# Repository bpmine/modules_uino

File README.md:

# modules_uino
Quelques modules à base d'arduino

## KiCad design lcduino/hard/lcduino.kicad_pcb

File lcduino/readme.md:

# LCDUINO - Ecran LCD Wifi déporté

Cet écran connecté permet d'afficher des informations fournies sur le réseau.

Un bouton permet d'interragir avec l'écran:
- Mise en veille
- Acquittement d'un message
- Réveil

## Mode d'emploi

Le boîtier est connecté en permanence au réseau local. Un serveur ouvert permet à un client du réseau d'envoyer des messages et des commandes à l'écran. Le boîtier est donc toujours accessible.

L'écran passe en veille au bout d'une heure.
Un appui sur le bouton permet de réveiller l'écran.

Un appui long sur le bouton fait passer l'écran en veille.

Lorsqu'un nouveau message est affiché, un symbole indique qu'il n'est pas encore lu. Pour marquer le message comme lu, l'utilisateur appuye brièvement sur le bouton. Le message est alors acquitté.

Un site web est accessible en permanance. Il permet de:
- Indiquer ce qui est actuellement affiché à l'écran
- Indiquer si le dernier message a été acquitté ou non
- Afficher un nouveau message
- Envoyer des commandes (ex: Afficher un chat, un chien, faire bip, ...)

## Carte électronique

Voir le dossier hard

## Logiciel

Voir le dossier src

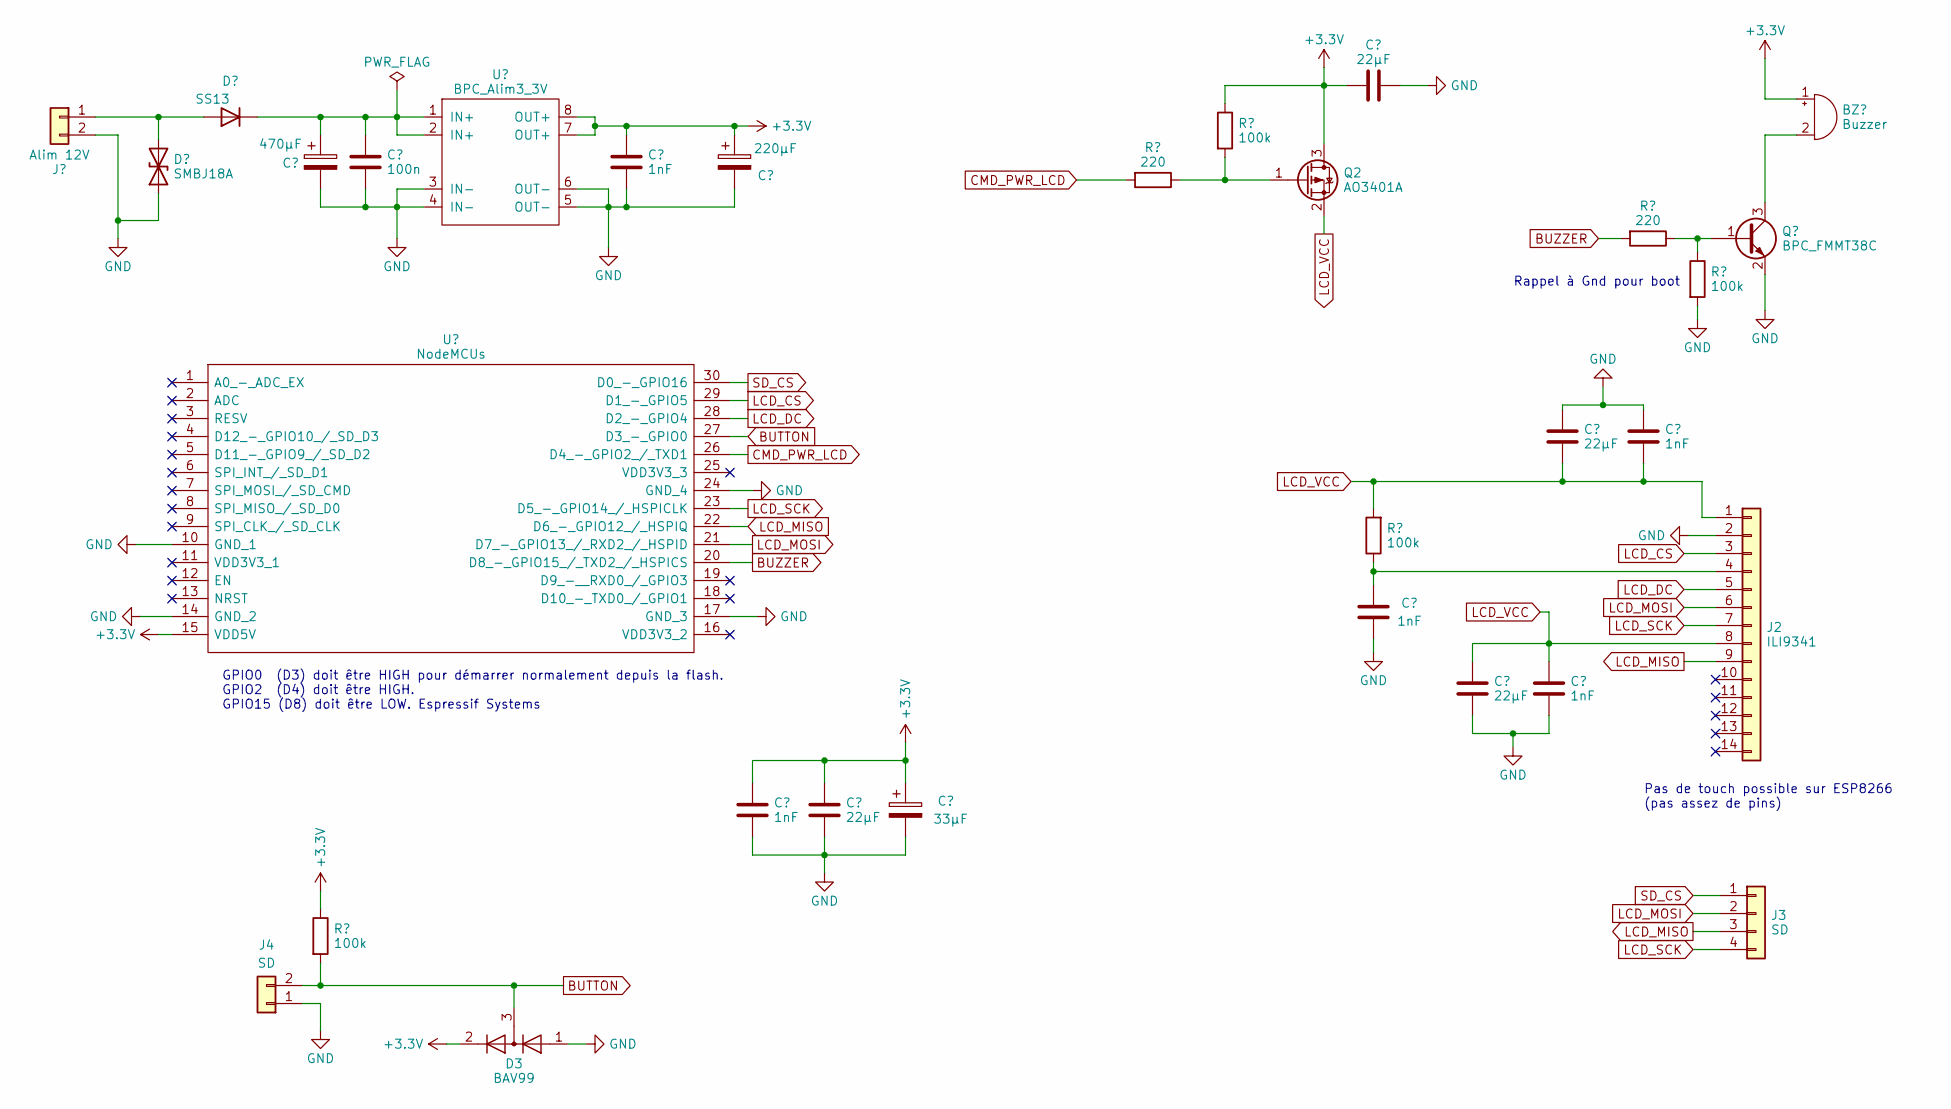
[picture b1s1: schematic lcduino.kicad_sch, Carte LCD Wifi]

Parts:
BZ1: Buzzer; MagneticBuzzer_ProSignal_ABT-410-RC
C1: 470µF; CP_Elec_8x10
C2: 100n; C_0805_2012Metric_Pad1.18x1.45mm_HandSolder
C3, C5, C8, C9, C13: 1nF; C_0805_2012Metric_Pad1.18x1.45mm_HandSolder
C4: 220µF; CP_Elec_6.3x5.3
C6, C10, C11, C12: 22µF; C_1206_3216Metric_Pad1.33x1.80mm_HandSolder
C7: 33µF; CP_Elec_4x5.3
D1: SMBJ18A; D_SMB_Handsoldering
D2: SS13; D_SMA
D3: BAV99; SOT-23
J1: Alim 12V; TerminalBlock_Phoenix_MKDS-1,5-2-5.08_1x02_P5.08mm_Horizont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
J2: ILI9341; PinSocket_1x14_P2.54mm_Vertical
J3: SD; PinSocket_1x04_P2.54mm_Vertical
J4: SD; JST_EH_B2B-EH-A_1x02_P2.50mm_Vertical
Q1: BPC_FMMT38C; BPC_SOT-23-3_HandSoldering
Q2: AO3401A; SOT-23
R1, R3: 220; R_0805_2012Metric_Pad1.20x1.40mm_HandSolder
R2, R4, R5, R6: 100k; R_0805_2012Metric_Pad1.20x1.40mm_HandSolder
U1: NodeMCUs; BPC_NodeMCU_small; Manufacturer_Part_Number 113990105; Mouser Part Number 713-113990105
U2: BPC_Alim3_3V

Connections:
+3.3V: BZ1.1 (-), C3.1, C4.1, C5.1, C6.1, C7.1, C11.1, D3.2 (A), Q2.3 (D), R4.1, R6.1, U1.15 (VDD5V), U2.7 (OUT+), U2.8 (OUT+)
BUTTON: D3.3 (K), J4.2, R6.2, U1.27 (D3_-_GPIO0)
BUZZER: R1.2, U1.20 (D8_-_GPIO15_/_TXD2_/_HSPICS)
CMD_PWR_LCD: R3.2, U1.26 (D4_-_GPIO2_/_TXD1)
GND: C1.2, C2.2, C3.2, C4.2, C5.2, C6.2, C7.2, C8.1, C9.1, C10.1, C11.2, C12.2, C13.2, D1.1 (A1), D3.1 (K), J1.2, J2.2, J4.1, Q1.2 (E), R5.2, U1.10 (GND_1), U1.14 (GND_2), U1.17 (GND_3), U1.24 (GND_4), U2.3 (IN-), U2.4 (IN-), U2.5 (OUT-), U2.6 (OUT-)
LCD_CS: J2.3, U1.29 (D1_-_GPIO5)
LCD_DC: J2.5, U1.28 (D2_-_GPIO4)
LCD_MISO: J2.9, J3.3, U1.22 (D6_-_GPIO12_/_HSPIQ)
LCD_MOSI: J2.6, J3.2, U1.21 (D7_-_GPIO13_/_RXD2_/_HSPID)
LCD_SCK: J2.7, J3.4, U1.23 (D5_-_GPIO14_/_HSPICLK)
LCD_VCC: C9.2, C10.2, C12.1, C13.1, J2.1, J2.8, Q2.2 (S), R2.2
unnamed: BZ1.2 (+), Q1.3 (C)
unnamed: D1.2 (A2), D2.2 (A), J1.1
unnamed: C1.1, C2.1, D2.1 (K), U2.1 (IN+), U2.2 (IN+)
unnamed: C8.2, J2.4, R2.1
unnamed: Q1.1 (B), R1.1, R5.1
unnamed: Q2.1 (G), R3.1, R4.2
SD_CS: J3.1, U1.30 (D0_-_GPIO16)

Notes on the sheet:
GPIO0 (D3) doit être HIGH pour démarrer normalement depuis la flash. GPIO2 (D4) doit être HIGH. GPIO15 (D8) doit être LOW. Espressif Systems
Pas de touch possible sur ESP8266 (pas assez de pins)
Rappel à Gnd pour boot

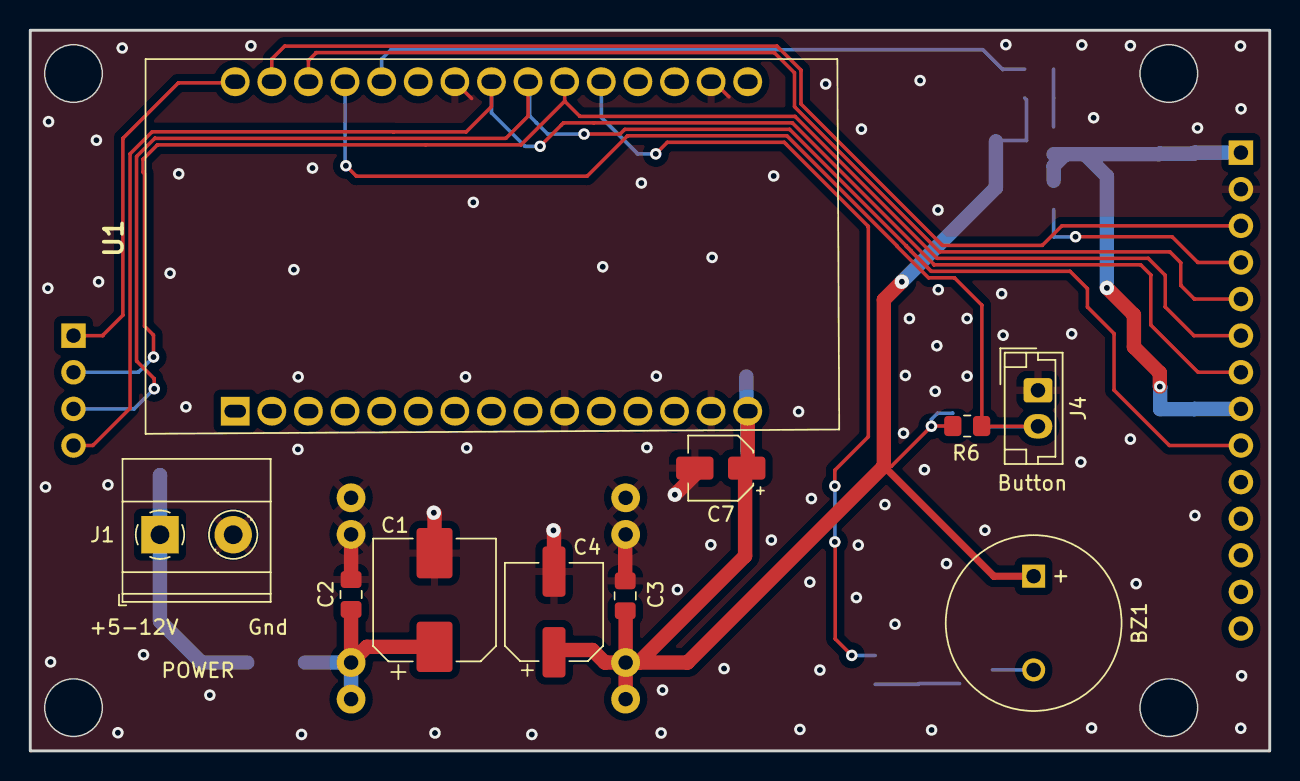
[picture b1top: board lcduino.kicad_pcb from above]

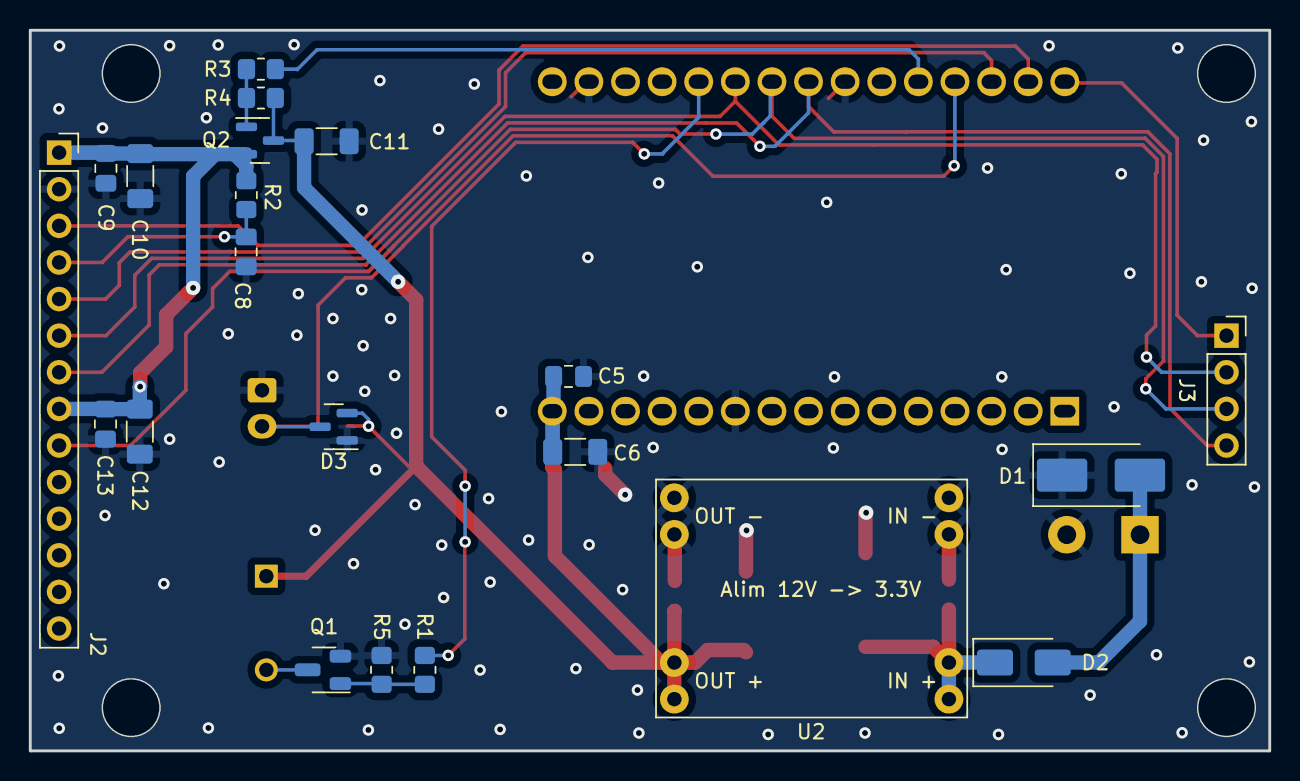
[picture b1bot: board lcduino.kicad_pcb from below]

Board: 2 copper layers, 86.0 x 50.0 mm, 31 parts (21 on the bottom side), 18 nets.

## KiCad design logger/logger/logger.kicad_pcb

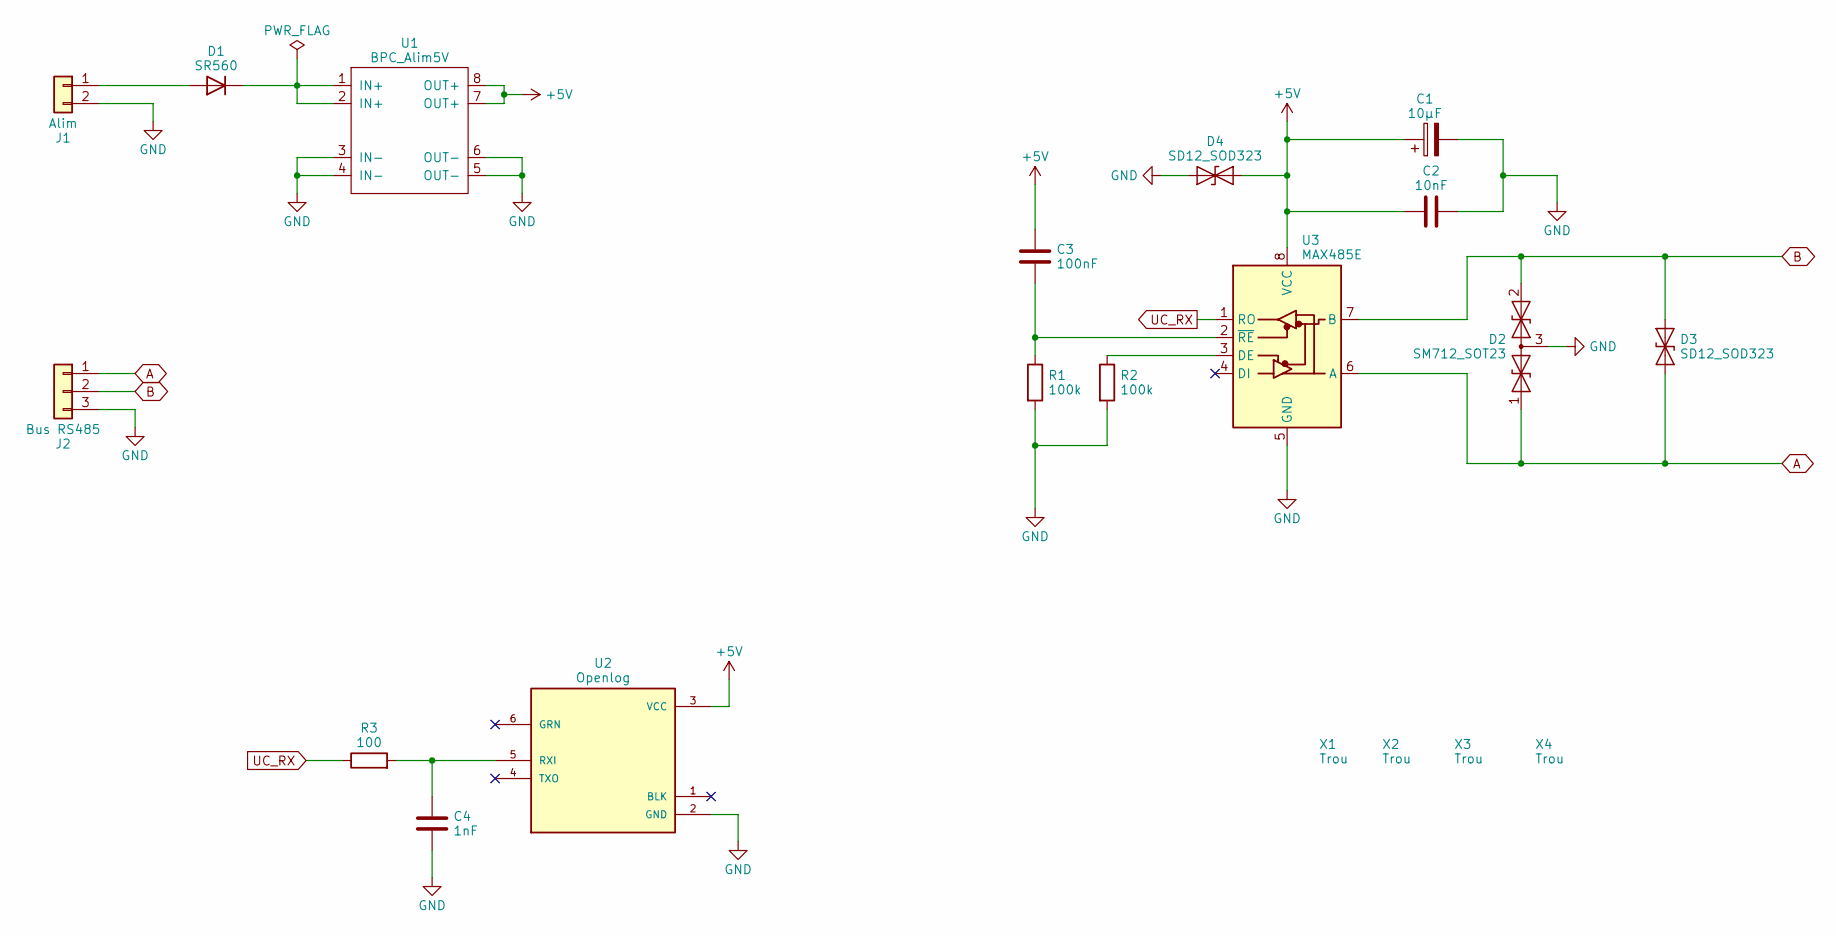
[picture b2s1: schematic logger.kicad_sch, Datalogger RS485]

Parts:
C1: 10µF; C_0805_2012Metric_Pad1.18x1.45mm_HandSolder
C2: 10nF; C_0805_2012Metric_Pad1.18x1.45mm_HandSolder
C3: 100nF; C_0805_2012Metric_Pad1.18x1.45mm_HandSolder
C4: 1nF; C_0805_2012Metric_Pad1.18x1.45mm_HandSolder
D1: SR560; D_DO-15_P12.70mm_Horizontal
D2: SM712_SOT23; SOT-23
D3, D4: SD12_SOD323; D_SOD-323
J1: Alim; TerminalBlock_Phoenix_MPT-0,5-2-2.54_1x02_P2.54mm_Horizontal
J2: Bus RS485; TerminalBlock_Phoenix_MPT-0,5-3-2.54_1x03_P2.54mm_Horizontal
R1, R2: 100k; R_0805_2012Metric_Pad1.20x1.40mm_HandSolder
R3: 100; R_0805_2012Metric_Pad1.20x1.40mm_HandSolder
U1: BPC_Alim5V
U2: Openlog; BPC_openlog; PARTREV v15
U3: MAX485E; BPC_MAX485E_SOIC127P600X175-8N
X1, X2, X3, X4: Trou; BPC_Trou4mm_Fixation

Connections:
+5V: C1.1, C2.1, C3.2, D4.1 (A1), U1.7 (OUT+), U1.8 (OUT+), U2.3 (VCC), U3.8 (VCC)
A: D2.1 (A1), D3.1 (A1), J2.1, U3.6 (A)
B: D2.2 (A2), D3.2 (A2), J2.2, U3.7 (B)
GND: C1.2, C2.2, C4.1, D2.3 (common), D4.2 (A2), J1.2, J2.3, R1.2, R2.2, U1.3 (IN-), U1.4 (IN-), U1.5 (OUT-), U1.6 (OUT-), U2.2 (GND), U3.5 (GND)
unnamed: D1.2 (A), J1.1
unnamed: D1.1 (K), U1.1 (IN+), U1.2 (IN+)
unnamed: C4.2, R3.2, U2.5 (RXI)
unnamed: R2.1, U3.3 (DE)
unnamed: C3.1, R1.1, U3.2 (~RE)
UC_RX: R3.1, U3.1 (RO)

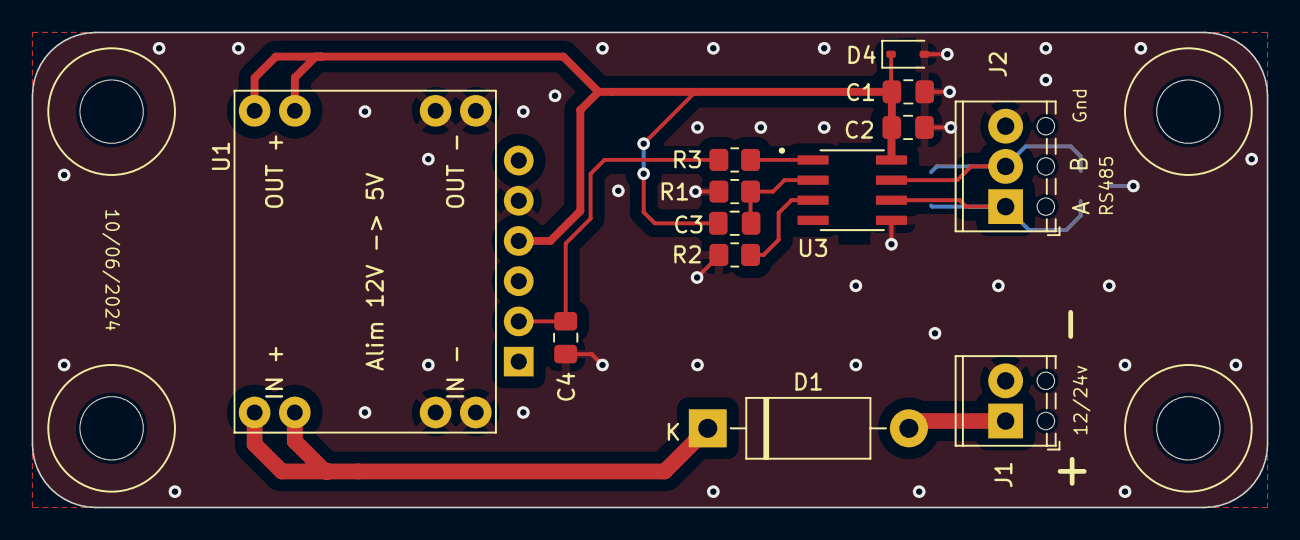
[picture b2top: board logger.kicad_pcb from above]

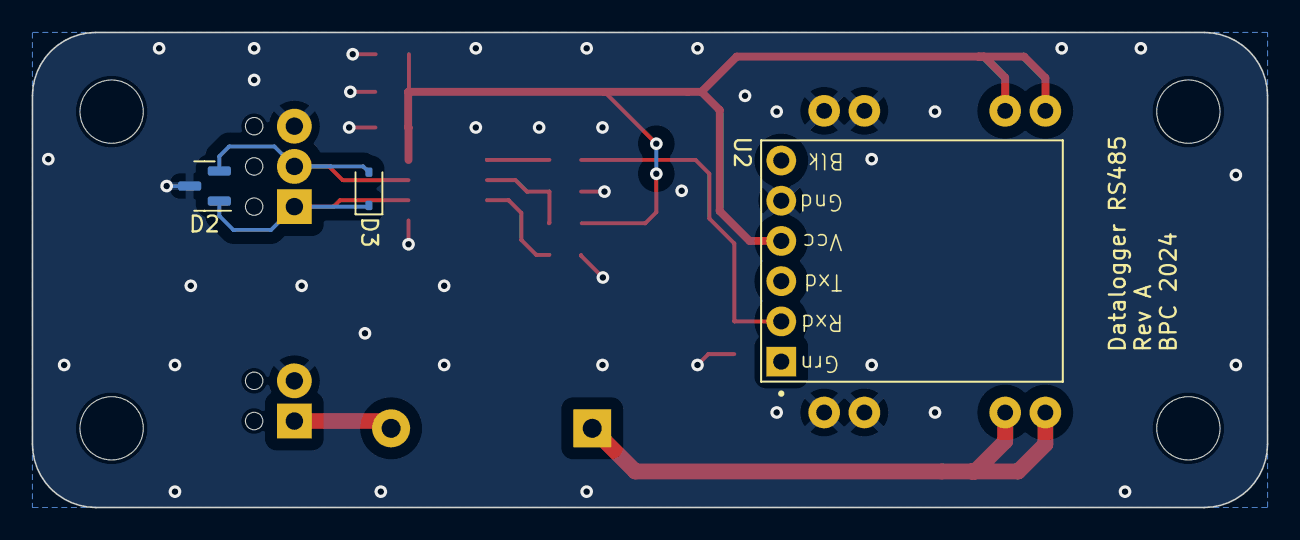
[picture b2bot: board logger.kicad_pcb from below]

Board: 2 copper layers, 78.0 x 30.0 mm, 20 parts (3 on the bottom side), 10 nets.

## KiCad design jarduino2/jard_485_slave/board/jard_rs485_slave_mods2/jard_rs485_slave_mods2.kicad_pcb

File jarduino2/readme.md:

# JARDUINO 2

Jarduino2 est une évolution du premier jarduino fabriqué en 2019.

Le premier jarduino était construit avec des platines de prototypage et un arduino MKR Zero Wifi.

Ce nouveau jarduino est construit à partir d'un Nano. On peut le configurer à l'aide d'une interface MODBUS sur l'USB ou bien sur le port série d'extension.
Il est possible de lui ajouter une extension Wifi pour le relier au réseau.

## Hardware

Caractéristiques:

  - Alimentation 12V;
  - Entrée de mesure de tension de panneau solaire;
  - 2 sorties 5W pour pompe (De type aquarium);
  - Sonde de température/Humidité;
  - LEDs et interrupteurs.

## Photos

## MODBUS

Le jarduino implémente un serveur/esclave MODBUS.

Seules les functions suivantes sont implémentées:

- 01 READ COIL STATUS
- 02 READ INPUT STATUS
- 03 READ HOLDING REGISTERS
- 04 READ INPUT REGISTERS
- 15 WRITE MULTIPLE COILS
- 16 WRITE MULTIPLE REGISTERS

### Table des COILs (Lecture/Ecriture)

Adresse | Description
--- | ---
10 | Forçage POMPE 1
11 | Autorisation/Activation POMPE 1
12 | Mode automatique POMPE 1
13 | Mode Distant POMPE 1
14 | Commande distante POMPE 1
--- | ---
20 | Forçage POMPE 2
21 | Autorisation/Activation POMPE 2
22 | Mode automatique POMPE 2
23 | Mode Distant POMPE 2
24 | Commande distante POMPE 2

Ces bits sont enregistrés en EEPROM sauf ceux qui correspondent au forçage des pompes et à leur commande distante.

NB: La commande à distance des pompe est appliquée seulement si le maître modbus communique toujours avec le jarduino nano.

### Table des Entrees (Lecture)

Adresse | Description
--- | ---
0 | Etat LED pompe 1
1 | Etat LED pompe 2
2 | Tension battery OK
3 | Tension panneau solaire OK
4 | Est en mode veille

### Table des INPUT REGISTERs (Lecture)

Adresse | Description
--- | ---
0 | Niveau de batterie en dxV
1 | Niveau du panneau solaire en dxV
2 | Temperature en °C
3 | Humidité en %
4 | Temps restant avant détection Comm perdue (en ms)
5 | Temps restant avant veille (en ms)
--- | ---
10 | Temps restant timer de pompe 1 (en min)
--- | ---
20 | Temps restant timer de pompe 2 (en min)
--- | ---
100 | Nombre total de boots
101 | Temps de fonctionnement total POMPE 1 (en H)
102 | Temps de fonctionnement total POMPE 1 (en H)
103 | Temps total d'ensoleillement (en H)
104 | Nombre total de pressions sur le bouton POMPE 1
104 | Nombre total de pressions sur le bouton POMPE 2
--- | ---
200 | Version (2 pour jarduino 2)
201 | Numéro de série du Jarduino
202 | Version du logiciel nano

### Table des HOLDING REGISTERs (Lecture/Ecriture)

Adresse | Description
--- | ---
0 | Année
1 | Mois
2 | Jour
3 | Heure
4 | Minute
5 | Seconde
--- | ---
10 | Heure de démarrage POMPE 1
11 | Minute de démarrage POMPE 1
12 | Durée (en min) d'activation de la POMPE 1
13 | Jours de la semaine pour l'activation de la POMPE 1 (Bit 0: Dimanche, Bit 1: Lundi, ..., Bit 7: Samedi)
14 | Réglage du délai du timer de pompe 1 (en min)
--- | ---
20 | Heure de démarrage POMPE 2
21 | Minute de démarrage POMPE 2
22 | Durée (en min) d'activation de la POMPE 2
23 | Jours de la semaine pour l'activation de la POMPE 2 (Bit 0: Dimanche, Bit 1: Lundi, ..., Bit 7: Samedi)
24 | Réglage du délai du timer de pompe 2 (en min)

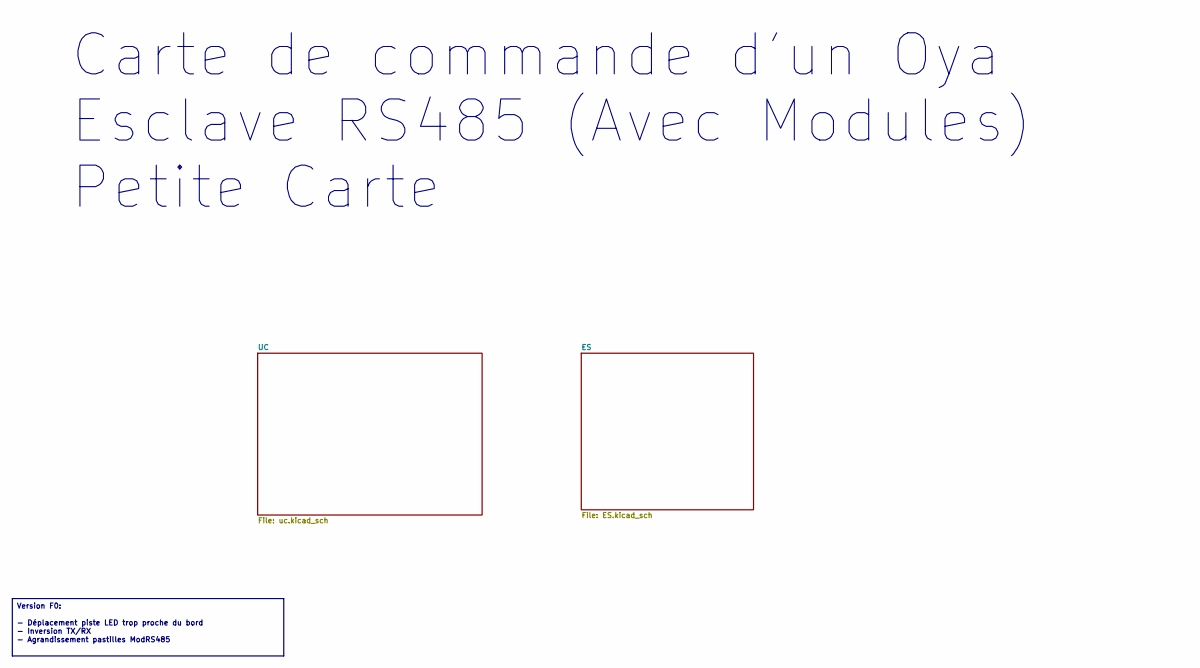
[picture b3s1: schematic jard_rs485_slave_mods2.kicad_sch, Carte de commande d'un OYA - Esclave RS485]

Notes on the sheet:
Version F0: - Déplacement piste LED trop proche du bord - Inversion TX/RX - Agrandissement pastilles ModRS485
Carte de commande d'un Oya Esclave RS485 (Avec Modules) Petite Carte

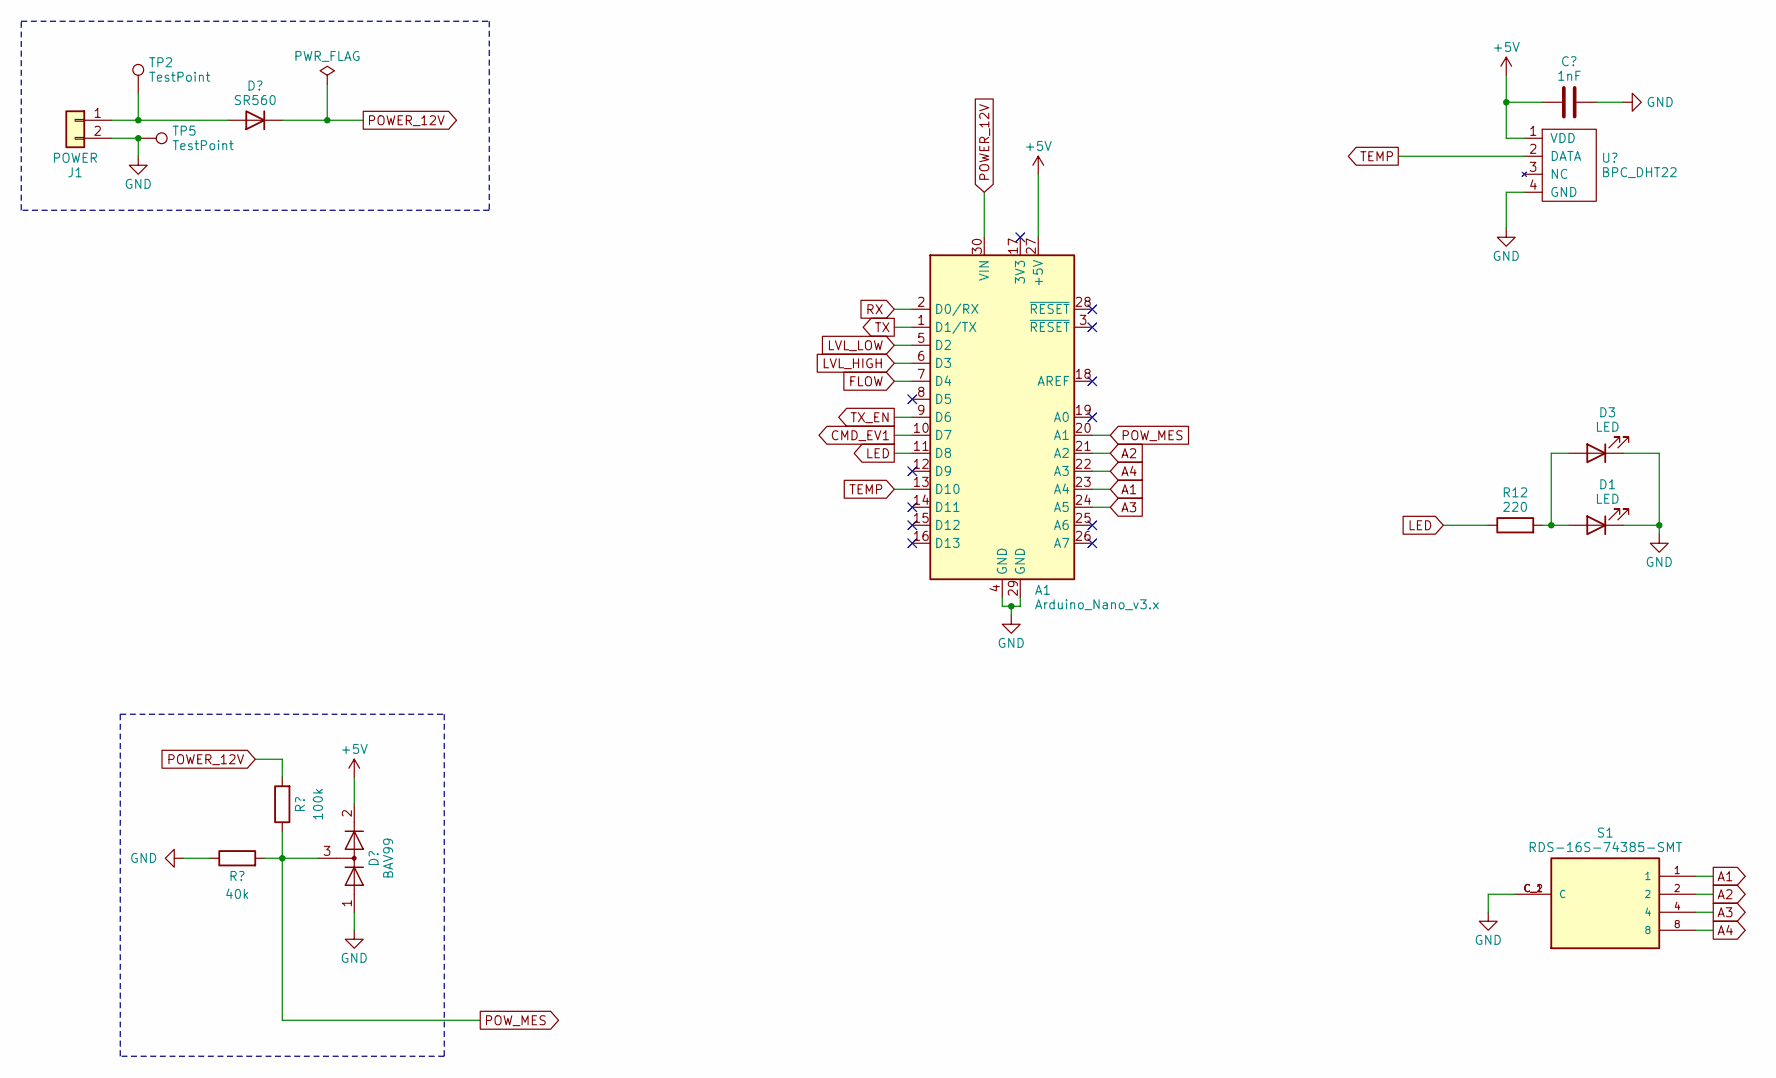
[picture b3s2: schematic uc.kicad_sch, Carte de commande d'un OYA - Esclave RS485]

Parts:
A1: Arduino_Nano_v3.x; BPC_Arduino_Nano
C7: 1nF; C_0603_1608Metric
D1: LED; LED_0805_2012Metric_Pad1.15x1.40mm_HandSolder
D2: SR560; D_DO-15_P12.70mm_Horizontal
D3: LED; LED_D3.0mm_FlatTop
D5: BAV99; SOT-23
J1: POWER; TerminalBlock_Phoenix_MKDS-1,5-2-5.08_1x02_P5.08mm_Horizont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
R1: 40k; R_0805_2012Metric_Pad1.20x1.40mm_HandSolder
R2: 100k; R_0805_2012Metric_Pad1.20x1.40mm_HandSolder
R12: 220; R_0805_2012Metric_Pad1.20x1.40mm_HandSolder
S1: RDS-16S-74385-SMT; BPC_RDS-16S-74385-SMT; PARTREV 1.0
TP2, TP5: TestPoint; TestPoint_Pad_D1.5mm
U6: BPC_DHT22

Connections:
+5V: A1.27 (+5V), C7.1, D5.2 (A), U6.1 (VDD); also elsewhere on the board
A1: A1.23 (A4), S1.1
A2: A1.21 (A2), S1.2
A3: A1.24 (A5), S1.4
A4: A1.22 (A3), S1.8
CMD_EV1: A1.10 (D7); also elsewhere on the board
FLOW: A1.7 (D4); also elsewhere on the board
GND: A1.4 (GND), A1.29 (GND), C7.2, D1.1 (K), D3.1 (K), D5.1 (K), J1.2, R1.1, S1.C_1 (C), S1.C_2 (C), TP5.1, U6.4 (GND); also elsewhere on the board
LED: A1.11 (D8), R12.1
LVL_HIGH: A1.6 (D3); also elsewhere on the board
LVL_LOW: A1.5 (D2); also elsewhere on the board
unnamed: D1.2 (A), D3.2 (A), R12.2
unnamed: D2.2 (A), J1.1, TP2.1
POWER_12V: A1.30 (VIN), D2.1 (K), R2.2; also elsewhere on the board
POW_MES: A1.20 (A1), D5.3 (K), R1.2, R2.1
RX: A1.2 (D0/RX); also elsewhere on the board
TEMP: A1.13 (D10), U6.2 (DATA)
TX: A1.1 (D1/TX); also elsewhere on the board
TX_EN: A1.9 (D6); also elsewhere on the board

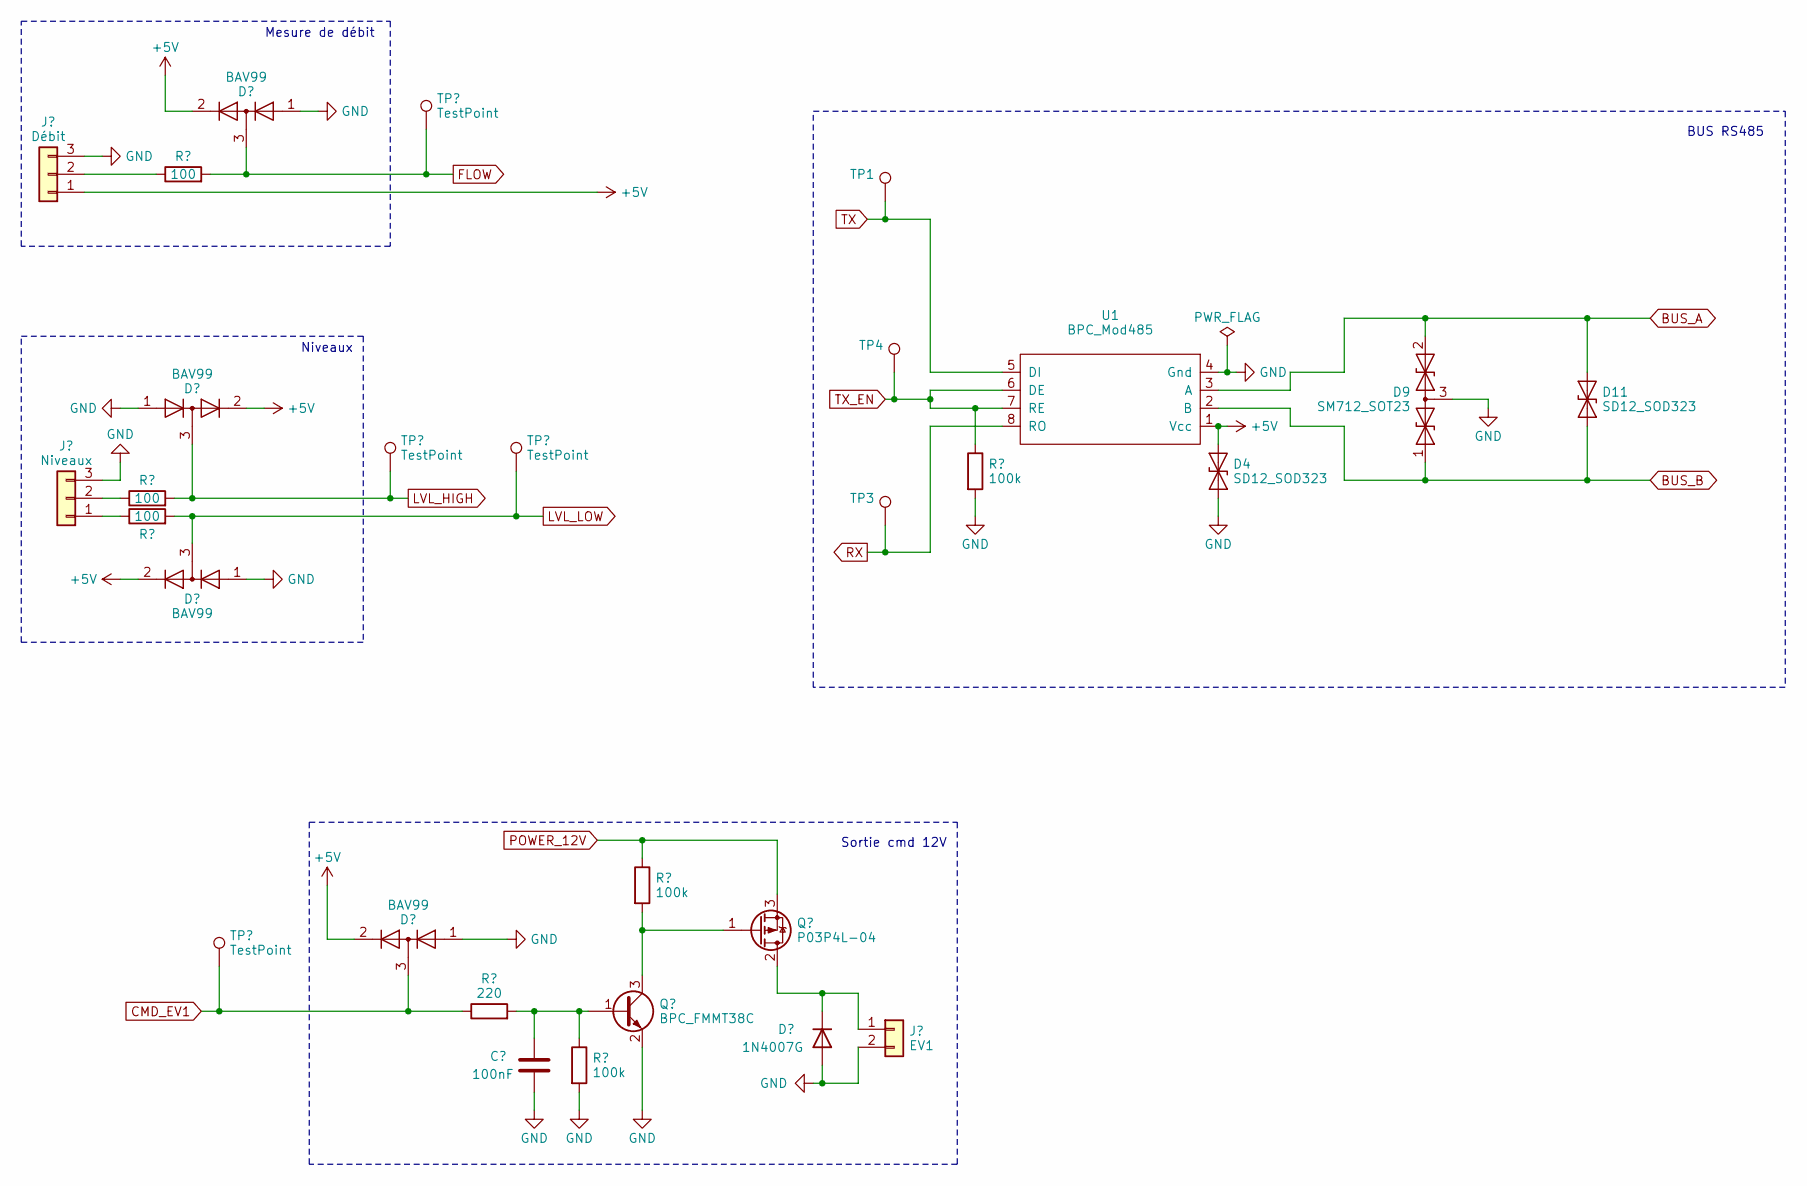
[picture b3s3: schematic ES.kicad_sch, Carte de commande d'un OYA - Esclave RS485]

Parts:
C6: 100nF; C_0603_1608Metric
D4, D11: SD12_SOD323; D_SOD-323
D6, D7, D8, D10: BAV99; SOT-23
D9: SM712_SOT23; SOT-23
D13: 1N4007G; D_A-405_P5.08mm_Vertical_KathodeUp
J3: Débit; TerminalBlock_Phoenix_MPT-0,5-3-2.54_1x03_P2.54mm_Horizontal
J4: Niveaux; TerminalBlock_Phoenix_MPT-0,5-3-2.54_1x03_P2.54mm_Horizontal
J6: EV1; TerminalBlock_Phoenix_MPT-0,5-2-2.54_1x02_P2.54mm_Horizontal
Q4: BPC_FMMT38C; BPC_SOT-23-3
Q6: P03P4L-04; TO-220-3_Vertical
R3, R15, R17: 100k; R_0805_2012Metric_Pad1.20x1.40mm_HandSolder
R7, R8, R9: 100; R_0805_2012Metric_Pad1.20x1.40mm_HandSolder
R13: 220; R_0805_2012Metric_Pad1.20x1.40mm_HandSolder
TP1, TP3, TP4, TP11, TP12, TP13, TP15: TestPoint; TestPoint_Pad_D1.5mm
U1: BPC_Mod485

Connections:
+5V: D4.1 (A1), D6.2 (A), D7.2 (A), D8.2 (A), D10.2 (A), J3.1, U1.1 (Vcc); also elsewhere on the board
BUS_A: D9.2 (A2), D11.2 (A2), U1.3 (A)
BUS_B: D9.1 (A1), D11.1 (A1), U1.2 (B)
CMD_EV1: D10.3 (K), R13.1, TP15.1; also elsewhere on the board
FLOW: D8.3 (K), R7.2, TP11.1; also elsewhere on the board
GND: C6.2, D4.2 (A2), D6.1 (K), D7.1 (K), D8.1 (K), D9.3 (common), D10.1 (K), D13.2 (A), J3.3, J4.3, J6.2, Q4.2 (E), R3.2, R15.2, U1.4 (Gnd); also elsewhere on the board
LVL_HIGH: D6.3 (K), R8.2, TP12.1; also elsewhere on the board
LVL_LOW: D7.3 (K), R9.2, TP13.1; also elsewhere on the board
unnamed: D13.1 (K), J6.1, Q6.2 (D)
unnamed: J3.2, R7.1
unnamed: J4.1, R9.1
unnamed: J4.2, R8.1
unnamed: C6.1, Q4.1 (B), R13.2, R15.1
unnamed: Q4.3 (C), Q6.1 (G), R17.2
POWER_12V: Q6.3 (S), R17.1; also elsewhere on the board
RX: TP3.1, U1.8 (RO); also elsewhere on the board
TX: TP1.1, U1.5 (DI); also elsewhere on the board
TX_EN: R3.1, TP4.1, U1.6 (DE), U1.7 (RE); also elsewhere on the board

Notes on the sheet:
Mesure de débit
BUS RS485
Sortie cmd 12V
Niveaux

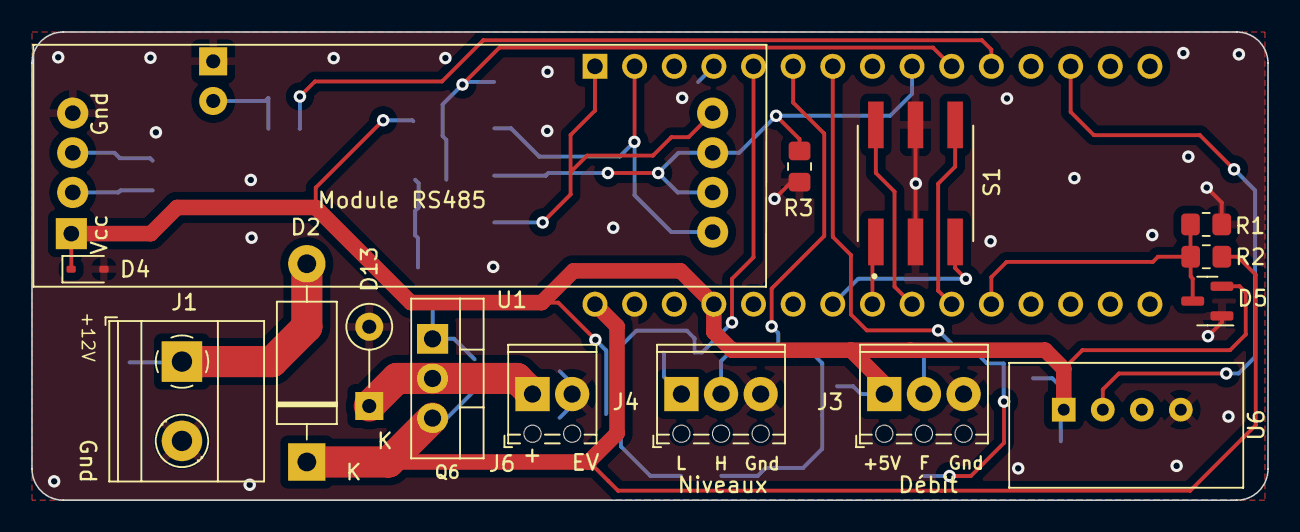
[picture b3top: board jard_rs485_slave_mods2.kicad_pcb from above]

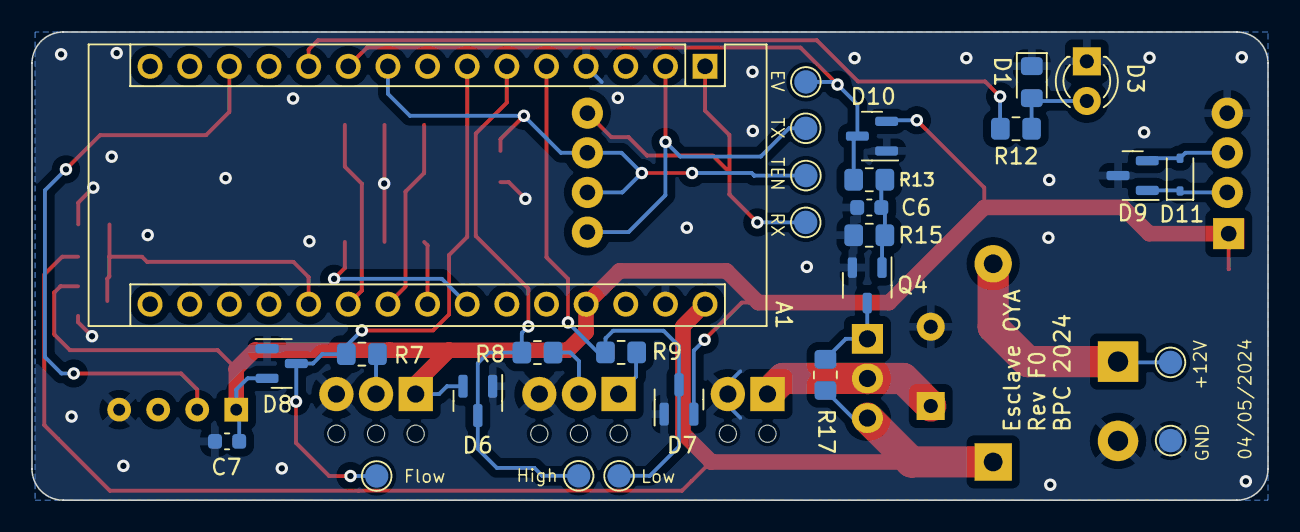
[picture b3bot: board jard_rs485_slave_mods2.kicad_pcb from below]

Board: 2 copper layers, 79.2 x 30.0 mm, 43 parts (28 on the bottom side), 27 nets.
